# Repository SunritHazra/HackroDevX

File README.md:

# HackroDevX

An open-source RP2040 development board with USB-C power/programming, onboard QSPI flash, and a Raspberry Pi Pico-compatible pinout. Built by following Hack Club's ["Custom Devboard"](https://blueprint.hackclub.com/starter-projects/devboard) starter project guide, entirely in KiCad. This is my first custom PCB from schematic to fabrication.

> Full day-by-day design log, decisions, and mistakes: [Engineering Log.md](https://github.com/SunritHazra/HackroDevX/blob/main/Engineering%20Log.md) (see also [JOURNAL.md](https://github.com/SunritHazra/HackroDevX/blob/main/JOURNAL.md) and [Fabrication Log.md](https://github.com/SunritHazra/HackroDevX/blob/main/Fabrication%20Log.md))

**Project stats:** 5 build-log days · ~25h 00m total design time · 100% designing progress, 0% building progress (as of the latest journal entry — board is ordered for PCBA, not yet assembled)

**On the name:** Follows the author's personal naming convention for electronics projects — "Hackro" as the base word, a short form of the project's defining trait ("Dev", for devboard), and a single trailing letter — giving **HackroDevX**.

---

## Renders

### Top View

### 45° View

### Bottom Corner View

---

## Hardware Architecture

### 1. Electrical Schematic

Full Schematic

The schematic follows the five functional blocks the guide breaks a devboard into: power/decoupling, USB-C, the crystal oscillator, QSPI flash storage, and the I/O breakout, all wired around a central RP2040.

**Power & decoupling:** One 0.1uF decoupling capacitor per RP2040 VDD pin — eight on the 3.3V IOVDD rail, two on the 1.1V DVDD rail — plus a 1uF bulk capacitor on each rail to smooth larger ripples. Power labels face up, ground labels face down, per standard schematic convention. [This](https://github.com/user-attachments/assets/96dde608-219d-472a-9682-96a95f16b071) is the power and decopuling.

**USB-C & step-down:** A USB-C receptacle with SHIELD/GND tied to ground, CC1/CC2 pulled down through 5.1KΩ resistors so the port negotiates power delivery, and the D+/D- lines routed through 27Ω termination resistors into the RP2040's USB_DP/USB_DM pins (set to bidirectional global labels). VBUS is stepped down from 5V to 3.3V using an **MCP1700x-330xxTT** LDO (swapped in from the guide's larger NCP1117-3.3_SOT223 for a smaller footprint, at the cost of a lower 250mA current limit), with 10uF bulk capacitors bracketing it. [This](https://github.com/user-attachments/assets/9e6f4866-57e1-4350-a7fc-b4eadb88d3cd) is the USB-C and step down.

**Crystal oscillator:** A 12MHz crystal (Y1) with two load capacitors on its I/O pins (bumped from the guide's 15pF to 33pF to match the load capacitance of the specific crystal part used), pins 2/4 tied to GND, and a 1KΩ damping resistor on XOUT to protect the crystal and keep the clock signal clean. [This](https://github.com/user-attachments/assets/4e26f85b-4016-400b-a56b-7d17701c3016) is the crystal ossilator.

**QSPI flash:** Since the RP2040 has no onboard flash, a quad-SPI flash IC is wired up with global labels matching the RP2040's QSPI pins, a 0.1uF decoupling cap on VCC, a 10KΩ pull-up on CS, and a BOOTSEL push button in series with a 1KΩ current-limiting resistor to GND — dropping the board into BOOTSEL/mass-storage mode on boot. [This](https://github.com/user-attachments/assets/fbd2d72e-f6a8-4ca6-835c-226b7e35d64e) is the onboard QSPI flash.

**I/O breakout:** TESTEN tied to GND (factory-test-only pin), and every remaining GPIO plus SWCLK/SWDIO broken out across two 1x20 headers and one 1x3 header, laid out to match the Raspberry Pi Pico pinout. VSYS, 3V3_EN, and ADC_VREF were skipped since there's no battery support, freeing up pins for extra GPIOs — including GPIO29 (ADC-capable) in place of the unused GPIO25. [This](https://github.com/user-attachments/assets/0c8a8f67-9cef-4537-8e4d-47fdbf4ebf10) is the I/O pins broken out.

### 2. Footprints

- **RP2040:** `QFN-56-1EP_7x7mm_P0.4mm_EP3.2x3.2mm`, straight from the datasheet.
- **Decoupling capacitors:** `0402` for all small signal capacitors.
- **Decopuling resistors:** `0402` for all small resistors.
- **Bulk (10uF) capacitors:** `0603`, for the extra physical room they need.
- **USB-C receptacle:** `USB_C_Receptacle_HRO_TYPE-C-31-M-12` — JLCPCB has no true basic-library USB-C part.
- **Header pins:** `PinHeader_1x20_P2.54mm_Vertical` (×2) and `PinHeader_1x03_P2.54mm_Vertical`.
- **Boot button:** `SW_Push_SPST_NO_Alps_SKRK`, a compact SMD footprint in JLCPCB's basic library.
- **Crystal:** `Crystal_SMD_3225-4Pin_3.2x2.5mm`, also a JLCPCB basic part — pin 1/3 orientation double-checked against the datasheet.
- **LDO:** `MCP1700x-330xxTT` (SOT-23), swapped from the NCP1117 for size.
- **Flash:** `W25Q16JVZPIQ TR` in the `Winbond_USON-8-1EP_3x2mm_P0.5mm_EP0.2x1.6mm` package — the same flash chip used on the real Pi Pico, swapped from the datasheet's larger W25Q128JVS.

### 3. Printed Circuit Board Assembly

Designed for rugged reliability and high-profile ergonomics using the custom footprints above.

KiCad PCB Window

KiCad PCB Render

KiCad PCBA Render

KiCad PCB Back Side

KiCad PCBA Back Side

- **Design files:** [`/PCBA`](./PCBA)

## Design Notes

**Board Size:** The board outline follows the guide's Pico-shaped form factor, sized **21mm × 51.5mm** (slightly longer than the guide's reference 21×51mm outline).

**Crystal load capacitance:** swapping to a different crystal part than the guide's reference meant the load capacitors had to be bumped from 15pF to 33pF to match its datasheet load capacitance.

**ERC net conflict:** an early wiring mistake merged the LDO's output and the RP2040's VREG_VOUT onto the same net (both flagged as power outputs), caused by using a slightly different LDO symbol than the guide's. Fixed by re-tracing the actual intended connections.

**Differential pair skew:** the USB D+/D- traces were initially routed without matching their lengths, resulting in a 6.5mm+ mismatch against a ~0.2mm budget — fixed by rerouting them as a proper differential pair.

**Silkscreen:** reference designators and values were batch-moved from the `F.Fab` layer to `F.Silkscreen` using KiCad's footprint text field batch update (filtered by layer, applied to functional text items). Less-useful `C#`/`R#` labels on small passives were deleted for a cleaner look, and bottom-side GPIO labels were checked for correct mirroring/orientation. The Hack Club "Orpheus" flag logo was thresholded through KiCad's Image Converter and placed on the silkscreen next to a `HackroDevX` text label and the author's name.**Silkscreen:** reference designators and values were batch-moved from the `F.Fab` layer to `F.Silkscreen` using KiCad's footprint text field batch update (filtered by layer, applied to functional text items). Less-useful `C#`/`R#` labels on small passives were deleted for a cleaner look, and bottom-side GPIO labels were checked for correct mirroring/orientation. The Hack Club "Orpheus" flag logo was thresholded through KiCad's Image Converter and placed on the silkscreen next to a `HackroDevX` text label and the author's name.

---

## Fabrication

- **Electrical Rule Check (ERC)** run after the schematic was completed.
- **Design Rule Check (DRC)** run after routing and ground pour, with thermal-relief/clearance errors resolved before export.
- **Gerber export:** full fabrication output (gerbers, drill files, footprint position files) exported from KiCad `9.0.7`.
- **CPL/BOM formatting for JLCPCB:** the CPL (`top-pos`) file headers were renamed `Ref → Designator`, `PosX → Mid X`, `PosY → Mid Y`, `Rot → Rotation`, `Side → Layer`, and the BOM's `Designation` column renamed to `Comment`, per JLCPCB's expected format.
- **Ordered:** production zip uploaded to JLCPCB with PCBA added for a batch of 5 assembled boards. Most parts auto-matched (RP2040 QFN-56, MCP1700x-330xxTT, USB-C receptacle, crystal, resistors, caps); the flash memory needed a manual match to JLCPCB's in-stock `W25Q16JVUXQTR` (functionally equivalent to the designed `W25Q16JVZPIQ TR`). Pin headers were left off the assembled parts list to hand-solder separately instead of paying per-part assembly fees.

Design files: [`/PCBA`](https://github.com/SunritHazra/HackroDevX/tree/main/PCBA)

---

## Bill of Materials (BOM)

JLCPCB BOM

JLCPCB BOM Tool - BOM Matching

Full sourcing sheet: [`/Bill of Materials`](https://github.com/SunritHazra/HackroDevX/tree/main/Bill%20of%20Materials)

### Electronics & PCB (SMD)

- **1x** PCB (21mm × 51.5mm, Pico-shaped outline)
- **1x** Raspberry Pi RP2040 SoC (QFN-56)
- **1x** W25Q16JVZPIQ TR QSPI flash memory
- **1x** MCP1700x-330xxTT LDO (3.3V, SOT-23)
- **1x** USB-C receptacle (HRO TYPE-C-31-M-12)
- **1x** 12MHz crystal oscillator (SMD 3225-4Pin)
- **1x** SPST push button (BOOTSEL)
- Decoupling capacitors (0402: 0.1uF ×10, 1uF ×2), bulk capacitors (0603: 10uF ×2), termination resistors (27Ω ×2), pull-up/pull-down/damping resistors (5.1KΩ, 10KΩ, 1KΩ)

### Hardware (THT)

- **2x** `PinHeader_1x20_P2.54mm_Vertical`
- **1x** `PinHeader_1x03_P2.54mm_Vertical`

### Sourcing

| Component            | Vendor  |
| --------------------- | ------- |
| PCB Fabrication & PCBA | JLCPCB  |

JLCPCB Order

--

## AI as a Research & Documentation Aid

The schematic, footprint selection, PCB layout, routing, and all fabrication decisions were done manually by following the Hack Club guide and the RP2040 datasheet. AI tools were used only in a supporting role — for example, researching general approaches to fixing a stubborn DRC thermal-relief/clearance error, and for helping structure and write up this documentation.

> **Project Integrity:** All schematic wiring, footprint selection, PCB routing, and fabrication file prep were done manually in KiCad by following the Hack Club Devboard guide and the RP2040 datasheet. AI was used only for research, troubleshooting suggestions, and documentation help.

---

## License

This project is licensed under the MIT License — see the [LICENSE](https://github.com/SunritHazra/HackroDevX/blob/main/LICENSE) file for details.

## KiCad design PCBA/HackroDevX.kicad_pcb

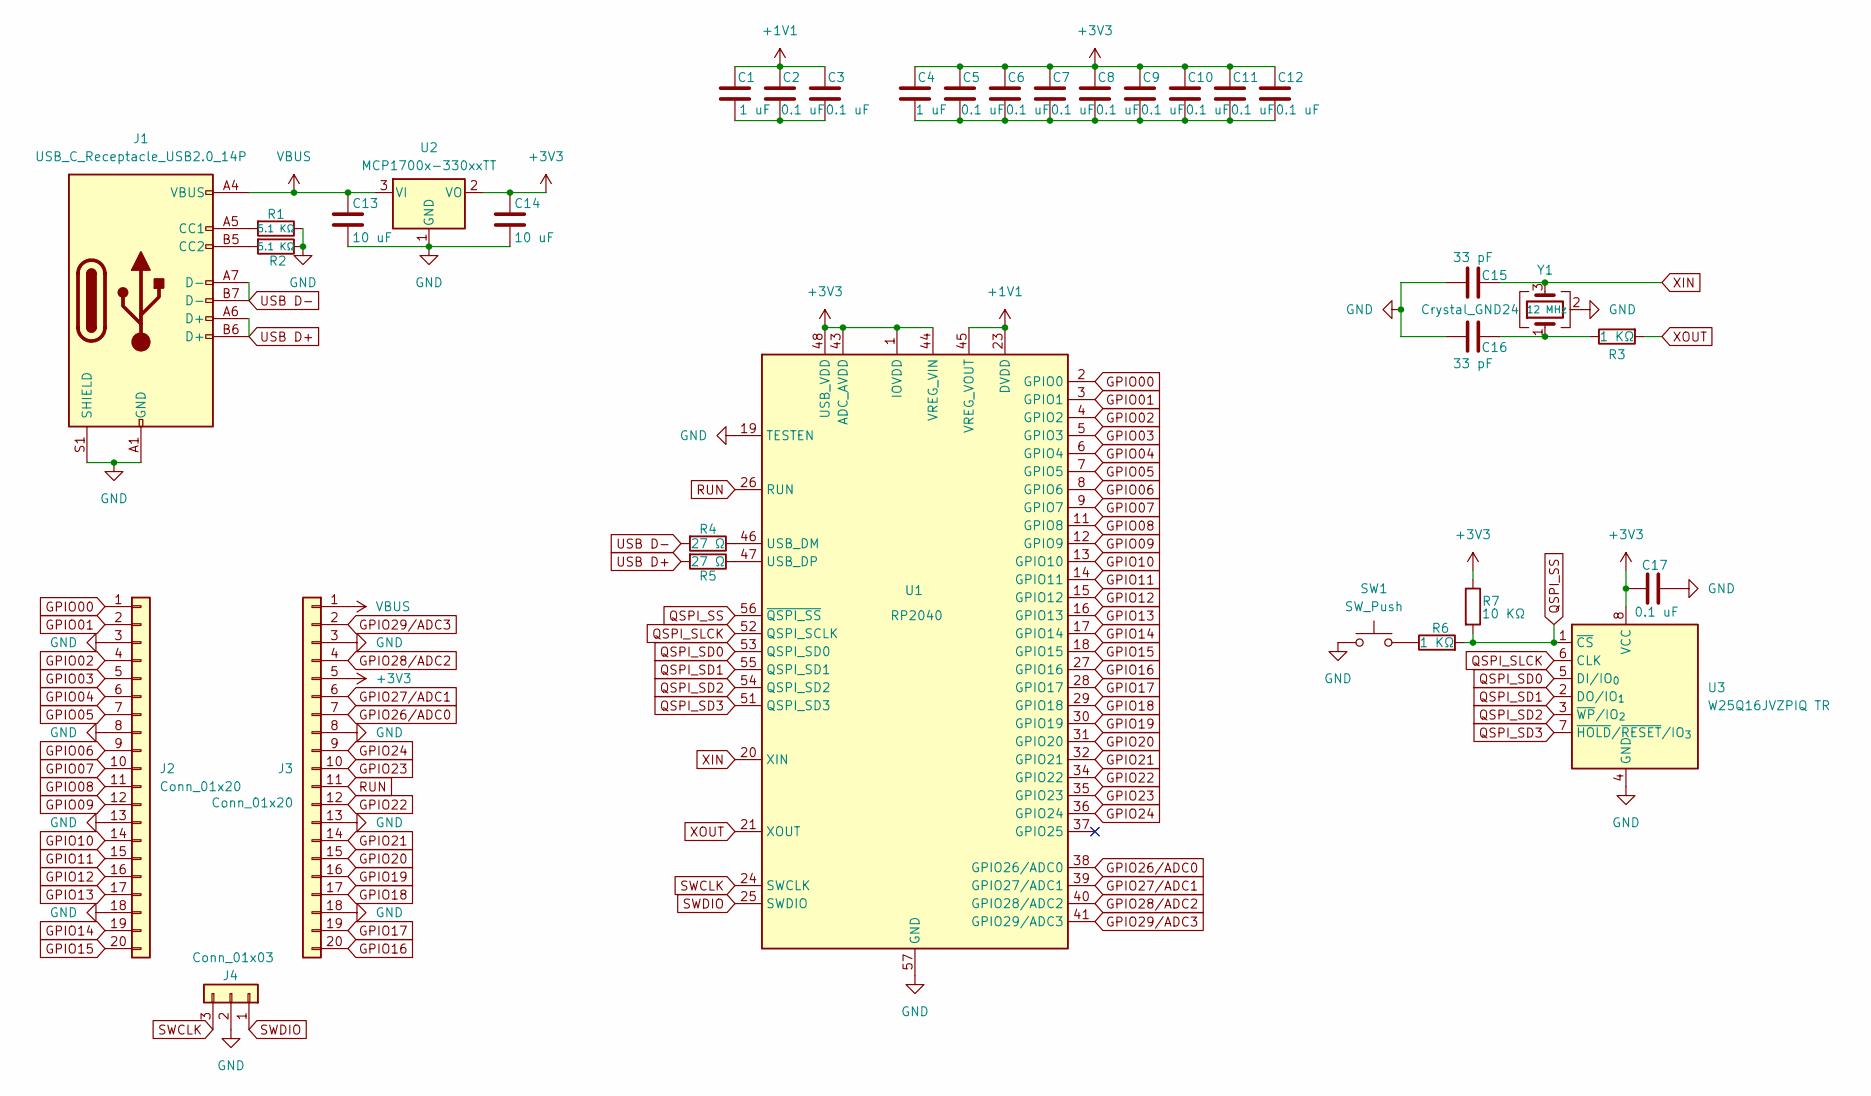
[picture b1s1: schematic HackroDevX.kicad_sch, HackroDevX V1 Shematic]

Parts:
C1, C4: 1 uF; C_0402_1005Metric
C2, C3, C5, C6, C7, C8, C9, C10, C11, C12, C17: 0.1 uF; C_0402_1005Metric
C13, C14: 10 uF; C_0603_1608Metric
C15, C16: 33 pF; C_0402_1005Metric
J1: USB_C_Receptacle_USB2.0_14P; USB_C_Receptacle_HRO_TYPE-C-31-M-12
J2, J3: Conn_01x20; PinHeader_1x20_P2.54mm_Vertical
J4: Conn_01x03; PinHeader_1x03_P2.54mm_Vertical
R1, R2: 5.1 KΩ; R_0402_1005Metric
R3, R6: 1 KΩ; R_0402_1005Metric
R4, R5: 27 Ω; R_0402_1005Metric
R7: 10 KΩ; R_0402_1005Metric
SW1: SW_Push; SW_Push_SPST_NO_Alps_SKRK
U1: RP2040; QFN-56-1EP_7x7mm_P0.4mm_EP3.2x3.2mm
U2: MCP1700x-330xxTT; SOT-23
U3: W25Q16JVZPIQ TR; Winbond_USON-8-1EP_3x2mm_P0.5mm_EP0.2x1.6mm
Y1: Crystal_GND24; Crystal_SMD_3225-4Pin_3.2x2.5mm

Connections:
+1V1: C1.1, C2.1, C3.1, U1.23 (DVDD), U1.45 (VREG_VOUT), U1.50 (DVDD)
+3V3: C4.1, C5.1, C6.1, C7.1, C8.1, C9.1, C10.1, C11.1, C12.1, C14.1, C17.1, J3.5, R7.1, U1.1 (IOVDD), U1.10 (IOVDD), U1.22 (IOVDD), U1.33 (IOVDD), U1.42 (IOVDD), U1.43 (ADC_AVDD), U1.44 (VREG_VIN), U1.48 (USB_VDD), U1.49 (IOVDD), U2.2 (VO), U3.8 (VCC)
GND: C13.2, C14.2, C15.1, C16.1, C17.2, J1.A1 (GND), J1.A12 (GND), J1.B1 (GND), J1.B12 (GND), J1.S1 (SHIELD), J2.3, J2.8, J2.13, J2.18, J3.3, J3.8, J3.13, J3.18, J4.2, R1.1, R2.1, SW1.1, U1.19 (TESTEN), U1.57 (GND), U2.1 (GND), U3.4 (GND), Y1.2 (G), Y1.4 (G)
GPIO00: J2.1, U1.2 (GPIO0)
GPIO01: J2.2, U1.3 (GPIO1)
GPIO02: J2.4, U1.4 (GPIO2)
GPIO03: J2.5, U1.5 (GPIO3)
GPIO04: J2.6, U1.6 (GPIO4)
GPIO05: J2.7, U1.7 (GPIO5)
GPIO06: J2.9, U1.8 (GPIO6)
GPIO07: J2.10, U1.9 (GPIO7)
GPIO08: J2.11, U1.11 (GPIO8)
GPIO09: J2.12, U1.12 (GPIO9)
GPIO10: J2.14, U1.13 (GPIO10)
GPIO11: J2.15, U1.14 (GPIO11)
GPIO12: J2.16, U1.15 (GPIO12)
GPIO13: J2.17, U1.16 (GPIO13)
GPIO14: J2.19, U1.17 (GPIO14)
GPIO15: J2.20, U1.18 (GPIO15)
GPIO16: J3.20, U1.27 (GPIO16)
GPIO17: J3.19, U1.28 (GPIO17)
GPIO18: J3.17, U1.29 (GPIO18)
GPIO19: J3.16, U1.30 (GPIO19)
GPIO20: J3.15, U1.31 (GPIO20)
GPIO21: J3.14, U1.32 (GPIO21)
GPIO22: J3.12, U1.34 (GPIO22)
GPIO23: J3.10, U1.35 (GPIO23)
GPIO24: J3.9, U1.36 (GPIO24)
GPIO26/ADC0: J3.7, U1.38 (GPIO26/ADC0)
GPIO27/ADC1: J3.6, U1.39 (GPIO27/ADC1)
GPIO28/ADC2: J3.4, U1.40 (GPIO28/ADC2)
GPIO29/ADC3: J3.2, U1.41 (GPIO29/ADC3)
unnamed: C1.2, C2.2, C3.2
unnamed: C4.2, C5.2, C6.2, C7.2, C8.2, C9.2, C10.2, C11.2, C12.2
unnamed: C16.2, R3.1, Y1.1
unnamed: J1.A5 (CC1), R1.2
unnamed: J1.B5 (CC2), R2.2
unnamed: R6.1, SW1.2
unnamed: R4.1, U1.46 (USB_DM)
unnamed: R5.1, U1.47 (USB_DP)
QSPI_SD0: U1.53 (QSPI_SD0), U3.5 (DI/IO_{0})
QSPI_SD1: U1.55 (QSPI_SD1), U3.2 (DO/IO_{1})
QSPI_SD2: U1.54 (QSPI_SD2), U3.3 (~WP/IO_{2})
QSPI_SD3: U1.51 (QSPI_SD3), U3.7 (~HOLD/~RESET/IO_{3})
QSPI_SLCK: U1.52 (QSPI_SCLK), U3.6 (CLK)
QSPI_SS: R6.2, R7.2, U1.56 (~QSPI_SS), U3.1 (~CS)
RUN: J3.11, U1.26 (RUN)
SWCLK: J4.3, U1.24 (SWCLK)
SWDIO: J4.1, U1.25 (SWDIO)
USB D+: J1.A6 (D+), J1.B6 (D+), R5.2
USB D-: J1.A7 (D-), J1.B7 (D-), R4.2
VBUS: C13.1, J1.A4 (VBUS), J1.A9 (VBUS), J1.B4 (VBUS), J1.B9 (VBUS), J3.1, U2.3 (VI)
XIN: C15.2, U1.20 (XIN), Y1.3
XOUT: R3.2, U1.21 (XOUT)

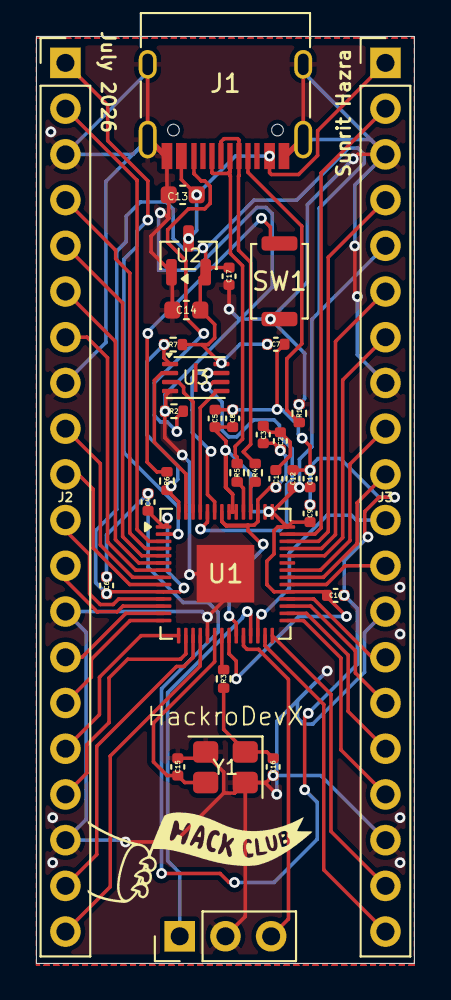
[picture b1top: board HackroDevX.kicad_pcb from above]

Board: 2 copper layers, 21.0 x 51.5 mm, 33 parts (0 on the bottom side), 54 nets.
